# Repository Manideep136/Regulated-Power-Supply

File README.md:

# Regulated-Power-Supply

Project Overview

This project is a Regulated Power Supply PCB designed using KiCad. The purpose of the circuit is to convert an unregulated DC input voltage into a stable and regulated DC output voltage.

The PCB is designed as a beginner-friendly electronics project to understand the complete PCB design process, including schematic design, component selection, footprint assignment, PCB layout, routing, ERC/DRC checking, and 3D visualization.

🎯 Objectives
Design a regulated DC power supply circuit.
Convert an input DC voltage into a stable output voltage.
Learn schematic design using KiCad.
Select appropriate footprints for electronic components.
Design and route a PCB.
Perform ERC and DRC checks.
Generate a 3D view of the completed PCB.
Understand the complete PCB design workflow.
⚡ Working Principle

The regulated power supply works in the following stages:

DC Input
An external DC voltage is supplied to the circuit through the input connector.
Filtering
Capacitors are used to reduce unwanted fluctuations and noise in the input voltage.
Voltage Regulation
A voltage regulator is used to maintain a constant output voltage even when the input voltage or load changes within the regulator's operating range.
Output Filtering
An additional capacitor helps stabilize the regulated output and reduce noise.
DC Output
The regulated voltage is available at the output connector and can be supplied to another electronic circuit.
Block Diagram
DC INPUT
   │
   ▼
Input Capacitor
   │
   ▼
Voltage Regulator
   │
   ▼
Output Capacitor
   │
   ▼
REGULATED DC OUTPUT
🧰 Components Used
Component	Quantity	Purpose
Voltage Regulator	1	Regulates the output voltage
Input Capacitor	1	Filters input voltage
Output Capacitor	1	Stabilizes output voltage
Resistors	As required	Current limiting / indication
LED	1	Power indication
Input Connector	1	DC input connection
Output Connector	1	Regulated output connection
PCB	1	Mounting and electrical connections

Note: The exact component values depend on the schematic used for this project.

🔌 Input and Output
Input

The input connector is used to provide DC power to the PCB.

INPUT
 +V  ─────────► Regulator
 GND ─────────► GND
Output

The regulator provides a stable DC voltage at the output connector.

OUTPUT
 +V_REG ──────► Load
 GND    ──────► Load

Always verify the input voltage and regulator rating before powering the PCB.

🖥️ Software Used
KiCad
KiCad Schematic Editor
KiCad PCB Editor
KiCad 3D Viewer
🧩 KiCad Design Process

The PCB was designed using the following workflow:

1. Schematic Design

The complete circuit was first created in KiCad Schematic Editor.

Components were placed and connected according to the circuit design.

2. Assign Footprints

Suitable footprints were assigned to each component according to the physical components that will be used.

Examples include:

Resistor_THT
Capacitor_THT
Package_TO_SOT_THT
Connector
LED

The exact footprint should always match the physical component purchased.

3. PCB Layout

The schematic was transferred to the PCB Editor.

Components were arranged on the PCB to obtain a compact and practical layout.

4. Routing

Tracks were created between the components according to the schematic connections.

Power and ground paths should be given appropriate track widths according to the expected current.

5. Design Rule Check

The PCB was checked using DRC (Design Rules Checker) to identify:

Unconnected tracks
Track clearance problems
Short circuits
Incorrect board geometry
Other PCB design-rule violations
6. 3D Visualization

KiCad's 3D Viewer was used to inspect the final PCB and verify component placement.

📁 Project Structure

A typical KiCad project contains:

Regulated-Power-Supply/
│
├── Regulated-Power-Supply.kicad_pro
├── Regulated-Power-Supply.kicad_sch
├── Regulated-Power-Supply.kicad_pcb
├── README.md
│
└── images/
    ├── schematic.png
    ├── pcb.png
    └── 3d-view.png
🔍 Important PCB Design Considerations
Check the polarity of capacitors.
Check the polarity of LEDs.
Verify regulator pin configuration.
Use the correct footprint for every component.
Keep power traces sufficiently wide.
Maintain proper clearance between PCB tracks.
Check all connector pin assignments.
Run ERC before PCB layout.
Run DRC after routing.
Verify the PCB using the 3D Viewer before fabrication.
🧪 Testing

After assembling the PCB:

Check the PCB visually for solder bridges and incorrect components.
Verify the polarity of all polarized components.
Check continuity between power and ground.
Apply the input voltage carefully.
Measure the output voltage using a multimeter.
Verify that the output remains close to the designed regulated voltage.
Connect the intended load and test the circuit again.
📚 What I Learned

Through this project, I learned:

How to create a schematic in KiCad.
How to select electronic components.
How to assign footprints.
How to transfer a schematic to PCB layout.
How to place components on a PCB.
How to route PCB tracks.
How to use ERC and DRC.
How to view a PCB in 3D.
How a voltage regulator is used in a power supply circuit.
Basics of designing a PCB suitable for fabrication.
🚀 Future Improvements

The project can be improved by adding:

Adjustable output voltage
Multiple output voltage levels
Reverse-polarity protection
Over-current protection
Fuse protection
Power-on LED indicator
Screw-terminal input/output
Larger heat sink for the regulator
USB output
Voltage and current display
⚠️ Safety
Do not exceed the maximum input voltage of the regulator.
Check capacitor voltage ratings before assembly.
Observe correct polarity.
Do not short-circuit the output.
If using a high-voltage AC source, use an appropriate isolated AC-to-DC stage and proper electrical safety practices. This PCB should not be connected directly to mains AC.
📸 Project Images

📌 Conclusion

The Regulated Power Supply PCB is a useful beginner KiCad project for understanding the complete PCB design process. It combines basic power-supply concepts with practical PCB design techniques such as schematic creation, footprint selection, component placement, routing, ERC, DRC, and 3D visualization.

This project provides a foundation for designing more advanced power supply, sensor, Arduino, ESP32, and IoT PCBs.

👨‍💻 Author

Manideep Kolluri

Project: Regulated Power Supply PCB
Tool: KiCad
Domain: Electronics / PCB Design

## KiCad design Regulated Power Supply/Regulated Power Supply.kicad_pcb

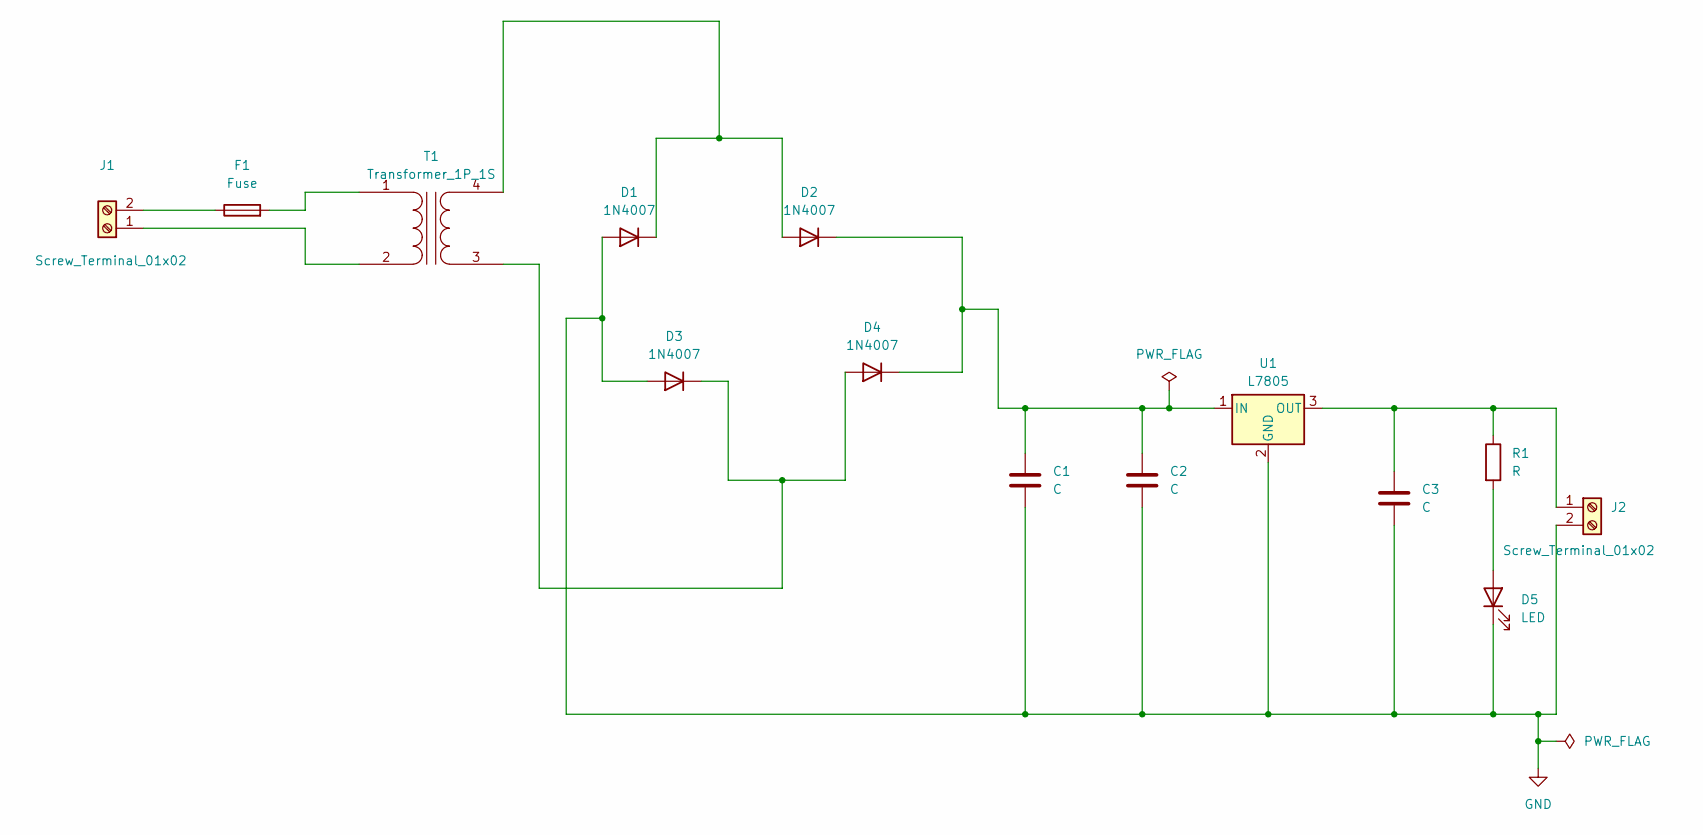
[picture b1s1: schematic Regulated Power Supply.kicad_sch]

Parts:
C1, C2, C3: C; CP_Radial_D10.0mm_P2.50mm_P5.00mm
D1, D2, D3, D4: 1N4007; D_DO-41_SOD81_P10.16mm_Horizontal
D5: LED; LED_D5.0mm
F1: Fuse; Fuseholder_Cylinder-5x20mm_Bulgin_FX0457_Horizontal_Closed
J1, J2: Screw_Terminal_01x02; TerminalBlock_Phoenix_MKDS-1,5-2_1x02_P5.00mm_Horizontal
R1: R; R_Axial_DIN0204_L3.6mm_D1.6mm_P5.08mm_Horizontal
T1: Transformer_1P_1S; Transformer_CHK_EI30-2VA_1xSec
U1: L7805; TO-220-3_Vertical

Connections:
GND: C1.2, C2.2, C3.2, D1.2 (A), D3.2 (A), D5.1 (K), J2.2, U1.2 (GND)
unnamed: D1.1 (K), D2.2 (A), T1.4 (SB)
unnamed: C1.1, C2.1, D2.1 (K), D4.1 (K), U1.1 (IN)
unnamed: D3.1 (K), D4.2 (A), T1.3 (SA)
unnamed: D5.2 (A), R1.2
unnamed: J1.1, T1.2 (AB)
unnamed: F1.1, J1.2
unnamed: C3.1, J2.1, R1.1, U1.3 (OUT)
unnamed: F1.2, T1.1 (AA)

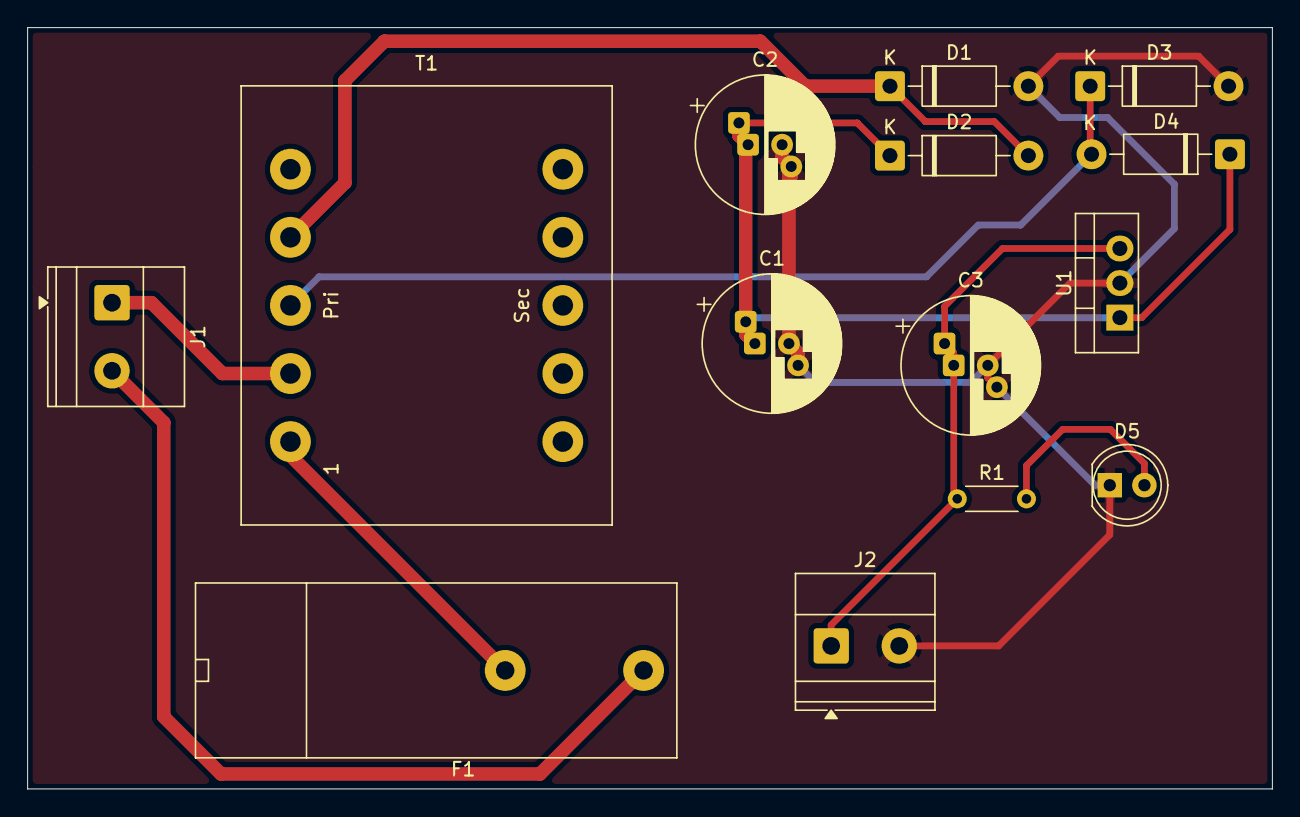
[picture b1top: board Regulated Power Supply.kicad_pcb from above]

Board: 2 copper layers, 91.4 x 55.9 mm, 14 parts (0 on the bottom side), 9 nets.
